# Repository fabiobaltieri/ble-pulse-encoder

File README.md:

# BLE Pulse Encoder

A replacement board, firmware and holder for converting a 60mm pulse encoder
jog wheel to Bluetooth Low Energy.

## License (firmware)

This program is free software: you can redistribute it and/or modify
it under the terms of the GNU General Public License as published by
the Free Software Foundation, either version 3 of the License, or
(at your option) any later version.

## License (hardware)

Hardware files are licensed under a
Creative Commons Attribution-ShareAlike 4.0 International License.

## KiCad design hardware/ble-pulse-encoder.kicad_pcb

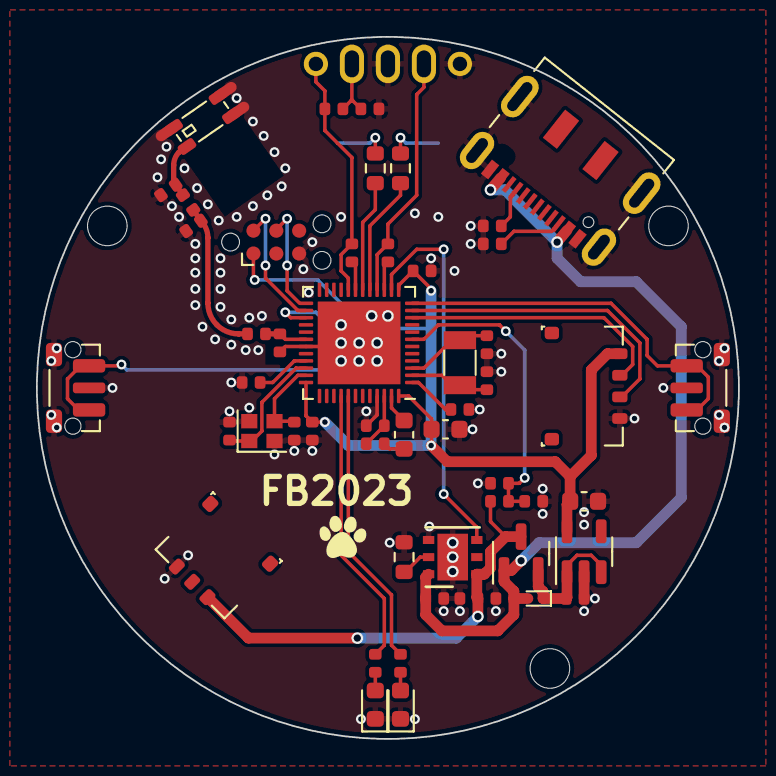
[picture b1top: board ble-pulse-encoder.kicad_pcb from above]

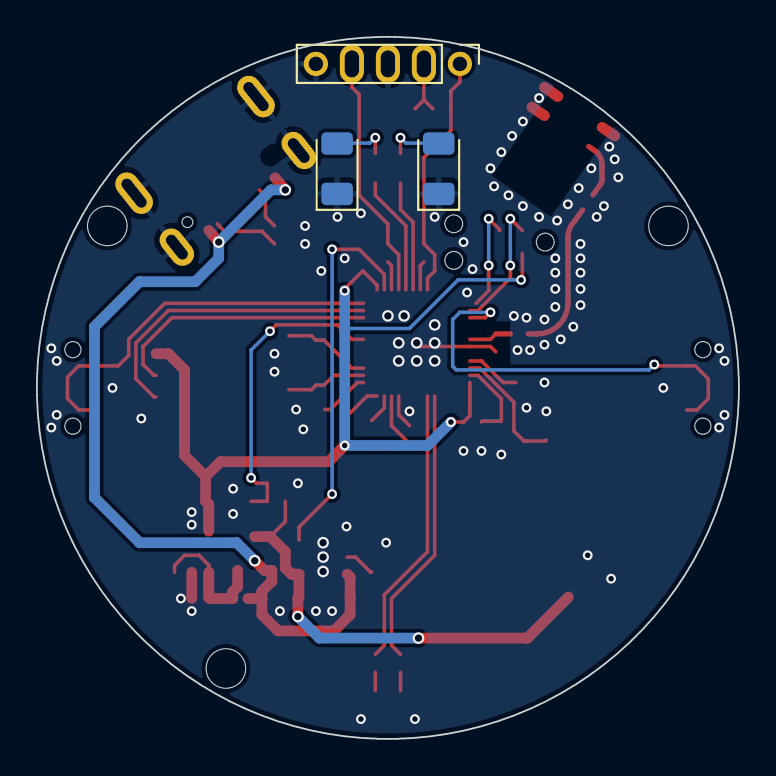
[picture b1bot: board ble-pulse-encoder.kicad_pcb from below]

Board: 2 copper layers, 39.0 x 39.0 mm, 58 parts (3 on the bottom side), 41 nets.

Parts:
AE1: 2450AT18D0100001; 2450AT18D0100001-L
C1, C2, C3, C4: 12p; C_0402_Worthington
C5, C6, C17: 1u; C_0402_Worthington
C7: 100p; C_0402_Worthington
C8, C9, C10, C12, C15: 100n; C_0402_Worthington
C11: 4.7u; C_0603_1608Metric
C13: 0.8p; C_0402_Worthington
C14, C16: TBD; C_0402_Worthington
C18: 10u; C_0603_1608Metric
D2: Green; LED_0603_1608Metric
D3: 1SS416; D_SOD-923
D4, D5: IR; LED_1206_3216Metric
D6: Yellow; LED_0603_1608Metric
H1, H2, H3: MountingHole_2.2mm_M2
J1: Conn_01x05; PinHeader_1x05_P2.00mm_Vertical
J2: EZmate-3
J3: EZmate-4
J4: TC2030-IDC-NL; Tag-Connect_TC2030-IDC-NL_2x03_P1.27mm_Vertical
J6: USB_C_Receptacle_USB2.0; USB_C_Receptacle_JAE_DX07S016JA1R1500
L1: 15n; L_0402_Worthington
L2: 10u; L_0603_1608Metric
L3: 3.9n; L_0402_Worthington
L4: 0; L_0402_Worthington
Q1: BSS84; SOT-23
R1: 2k2; R_0603_1608Metric
R2, R14: 5.1k; R_0402_Worthington
R3, R4: 560k; R_0402_Worthington
R5, R11, R12: 10k; R_0402_Worthington
R6, R13: 1k; R_0402_Worthington
R9, R10: 470; R_0603_1608Metric
R15, R16: 0; R_0402_Worthington
SW1, SW2: SW_Push; SW_Push_1P1T-MP_NO_Horizontal_Alps_SKRTLAE010
U1: STBC08; DFN-6-1EP_3x3mm_P0.95mm_EP1.7x2.6mm
U2: nRF52832-QFxx; QFN-48-1EP_6x6mm_P0.4mm_EP4.6x4.6mm
U3: TPS7A0333DBVR; SOT-23-5
Y1: 32.768kHz; Crystal_SMD_3215-2Pin_3.2x1.5mm
Y2: 32MHz; Crystal_SMD_2016-4Pin_2.0x1.6mm

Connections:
+3V3: C8.1, C10.1, C11.1, C18.1, J3.1, J4.1, U2.13 (VDD), U2.36 (VDD), U2.48 (VDD), U3.5 (OUT)
+5V: C6.1, D3.2 (A), J6.A4 (VBUS), J6.A9 (VBUS), J6.B4 (VBUS), J6.B9 (VBUS), Q1.1 (G), R5.1, U1.6 (VCC)
+BATT: C12.1, J2.1, Q1.3 (D), R3.1, U1.1 (BAT)
/ADC_VBATT: C15.1, R3.2, R4.1, U2.7 (P0.05/AIN3)
/ANT: C13.1, L3.2, U2.30 (ANT)
/CHRG: U1.3 (CHRG), U2.14 (P0.11)
/D0_PWR: R10.1, U2.17 (P0.14)
/D1_PWR: R9.1, U2.18 (P0.15)
/LED_A: R6.1, U2.40 (P0.28/AIN4)
/LED_B: R13.1, U2.41 (P0.29/AIN5)
/NRF_SWCLK: J4.4, U2.25 (SWDCLK)
/NRF_SWDIO: J4.2, U2.26 (SWDIO)
/PH0_PWR: R11.1, U2.15 (P0.12)
/PH0_SENSE: J1.4, R11.2, U2.16 (P0.13)
/PH1_PWR: R12.1, U2.19 (P0.16)
/PH1_SENSE: J1.1, R12.2, R15.1, U2.20 (P0.17)
/SW_A: SW1.1, U2.27 (P0.22)
/SW_B: SW2.1, U2.12 (NFC2/P0.10)
/UART_RX: J3.2, U2.10 (P0.08)
/UART_TX: J3.3, U2.11 (NFC1/P0.09)
/XL1: C2.1, U2.2 (P0.00/XL1), Y1.2
/XL2: C4.1, U2.3 (P0.01/XL2), Y1.1
GND: AE1.2 (Shield), C1.2, C2.2, C3.2, C4.2, C5.2, C6.2, C7.2, C8.2, C9.2, C10.2, C11.2, C12.2, C13.2, C14.2, C15.2, C16.2, C17.2, C18.2, D2.1 (K), D4.1 (K), D5.1 (K), D6.1 (K), J1.3, J1.5, J2.3, J3.4, J4.5, J6.A1 (GND), J6.A12 (GND), J6.B1 (GND), J6.B12 (GND), J6.S1 (SHIELD), R1.2, R2.2, R4.2, R5.2, R14.2, R16.2, SW1.2, SW1.MP, SW2.2, SW2.MP, U1.4 (GND), U1.7 (TH), U2.31 (VSS), U2.45 (VSS), U2.49 (VSS), U3.2 (GND), Y2.2, Y2.4
unnamed: AE1.1 (A), C16.1, L4.1
unnamed: C14.1, L3.1, L4.2
unnamed: D2.2 (A), R6.2
unnamed: D4.2 (A), R9.2
unnamed: D5.2 (A), R10.2
unnamed: D6.2 (A), R13.2
unnamed: J1.2, R15.2, R16.1
unnamed: J6.A5 (CC1), R14.1
unnamed: J6.B5 (CC2), R2.1
unnamed: L1.2, L2.2
unnamed: R1.1, U1.5 (PROG)
unnamed: L2.1, U2.47 (DCC)
unnamed: C9.1, U2.1 (DEC1)
unnamed: C7.1, U2.33 (DEC3)
unnamed: C5.1, L1.1, U2.46 (DEC4)
unnamed: C1.1, U2.34 (XC1), Y2.1
unnamed: C3.1, U2.35 (XC2), Y2.3
VCC: C17.1, D3.1 (K), Q1.2 (S), U3.1 (IN), U3.3 (EN)

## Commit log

2023-11-26 hw: initial import
2023-12-07 hw: few p/n tweaks
2023-12-13 hw: assembly notes
2023-12-13 fw: initial import
2023-12-13 add a .gitignore file
2023-12-13 fw: add input shell, set the led pins to high drive
2023-12-13 fw: set the chrg pin
2023-12-15 fw: add a couple labels
2023-12-15 fw: add a blank main
2023-12-17 fw: add ble hog stuff
2023-12-17 fw: flip a-b lines
2023-12-17 fw: fix adc channel
2023-12-17 fw: add bas adc
2023-12-17 hw: add note about missing vbatt line
2023-12-17 fw: disable serial by default
2023-12-18 hw: copy r0 files to r0/
2023-12-18 hw: r1
2023-12-31 hw: change D2 to blue
2024-01-18 cad: add some models
2024-01-18 cad: add some nut relief
2024-01-18 cad: base, bigger fillet
2024-01-23 fw: swap left and right buttons
2024-01-23 fw: add charging led handler
2024-01-23 fw: add blinker and ble status
2024-01-23 fw: missing static
2024-01-23 fw: tweak the disconnect blink
2024-01-23 fw: add qdec PM control
2024-01-25 fw: blink at boot
2024-01-26 fw: add flash_mcuboot
2024-01-26 fw: enable mcumgr
2024-01-26 fw: implement unpairing
2024-01-26 fw: enable bluetooths hell and minimal logging
2024-01-26 fw: add flash_ota.py
2024-01-27 fw: tweak few configs
2024-01-27 fw: reduce the main stack size
2024-02-02 add README.md
2024-02-02 fw: add a west.yaml file
2024-02-02 build: add build workflow
2024-02-02 build: add artifact upload
2024-02-20 fw: convert to hwmv2
2024-03-03 fw: use DT_PARENT to find the leds device
2024-03-05 fw: fix middle button code
2024-04-14 fw: shrink the shell backend dummy buffer size
2024-07-18 add tab cad file
2024-07-18 fw: drop part of zephyr-input-hid now
